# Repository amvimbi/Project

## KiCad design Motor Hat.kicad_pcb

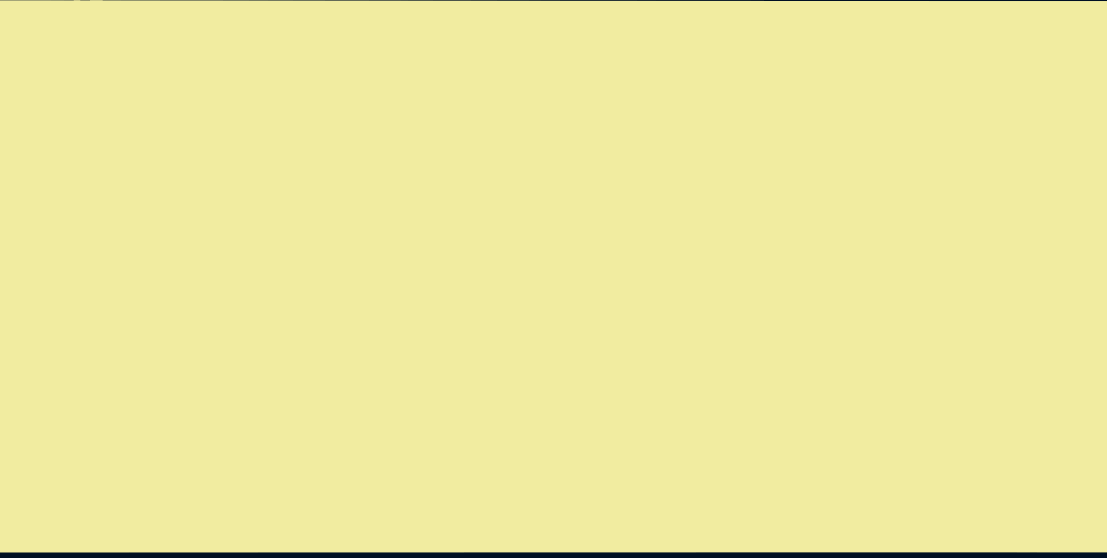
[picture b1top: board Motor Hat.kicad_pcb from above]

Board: 2 copper layers, 19 parts (0 on the bottom side), 10 nets.

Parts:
C1: C; CP_Axial_L10.0mm_D4.5mm_P15.00mm_Horizontal
C2: 100n; CP_Axial_L10.0mm_D4.5mm_P15.00mm_Horizontal
C3: 470u; CP_Axial_L10.0mm_D4.5mm_P15.00mm_Horizontal
D1: D_Zener; Diode_Bridge_Diotec_MicroDil_3.0x3.0x1.8mm
D2: DIODE; D_0603_1608Metric_Pad1.05x0.95mm_HandSolder
D3: BLUE LED; Diode_Bridge_Diotec_MicroDil_3.0x3.0x1.8mm
D4: RED LED; Diode_Bridge_Diotec_MicroDil_3.0x3.0x1.8mm
D5: GREEN LED; Diode_Bridge_Diotec_MicroDil_3.0x3.0x1.8mm
L1: L_Core_Ferrite; L_6.3x6.3_H3
Q1: Q_NMOS_DGS; DirectFET_MN
Q2: NPN; TO-92
Q3: 2N2219; TO-39-3
R1: 10k; Potentiometer_ACP_CA9-H3,8_Horizontal
R2: 1.2; R_Axial_DIN0204_L3.6mm_D1.6mm_P7.62mm_Horizontal
R3: 2.4k; R_0603_1608Metric_Pad1.05x0.95mm_HandSolder
R4: 430; R_0603_1608Metric_Pad1.05x0.95mm_HandSolder
R5: 62; R_0603_1608Metric_Pad1.05x0.95mm_HandSolder
R6: 43; R_0603_1608Metric_Pad1.05x0.95mm_HandSolder
U1: LM741; SuperSOT-3

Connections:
GND: C1.2, C2.2, C3.1, C3.2, D1.2, D2.1, D4.1, D5.1, Q2.2, Q3.1, R1.1, R1.3, R2.2
Motor: C2.1, D2.2, Q2.3, R2.1, U1.2
unnamed: D1.1, L1.1, Q1.3
unnamed: D3.1, Q3.3
unnamed: D3.2, R4.2
unnamed: D4.2, R5.2
unnamed: D5.2, R6.2
unnamed: Q3.2, R3.1
unnamed: R1.2, U1.3
Vout+: C1.1, L1.2

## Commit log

2021-06-04 Check the PCB
    amend and or change as necessary.
2021-06-04 Subsystems Folder
